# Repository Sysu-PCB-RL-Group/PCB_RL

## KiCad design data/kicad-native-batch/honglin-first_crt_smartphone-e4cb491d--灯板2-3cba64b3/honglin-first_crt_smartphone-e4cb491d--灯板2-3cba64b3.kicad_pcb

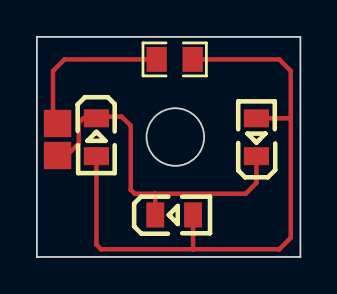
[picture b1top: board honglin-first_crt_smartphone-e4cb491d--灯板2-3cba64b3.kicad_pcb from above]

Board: 2 copper layers, 14.6 x 12.2 mm, 4 parts (0 on the bottom side), 2 nets.

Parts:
LED1, LED2, LED3: LED0805-R-RD
R2: R0805

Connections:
$1N488: LED1.1, LED2.1, LED3.1, R2.1
GND: LED1.2, LED2.2, LED3.2

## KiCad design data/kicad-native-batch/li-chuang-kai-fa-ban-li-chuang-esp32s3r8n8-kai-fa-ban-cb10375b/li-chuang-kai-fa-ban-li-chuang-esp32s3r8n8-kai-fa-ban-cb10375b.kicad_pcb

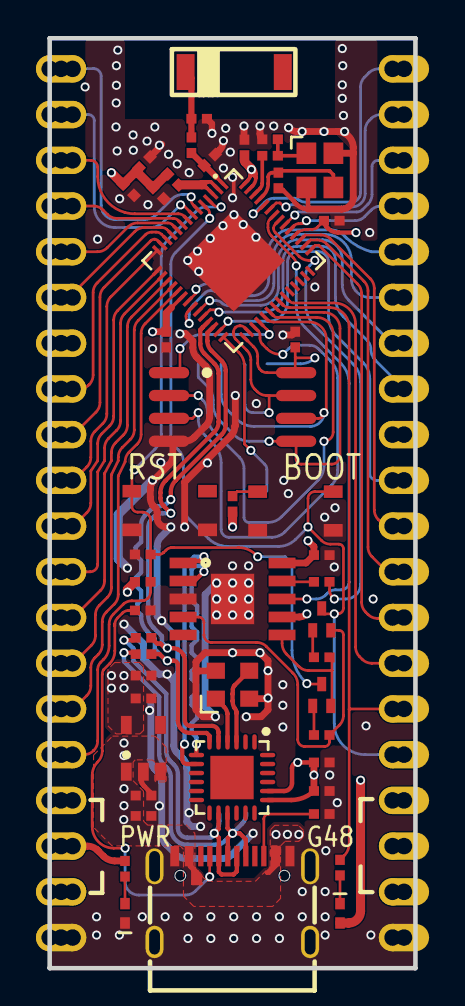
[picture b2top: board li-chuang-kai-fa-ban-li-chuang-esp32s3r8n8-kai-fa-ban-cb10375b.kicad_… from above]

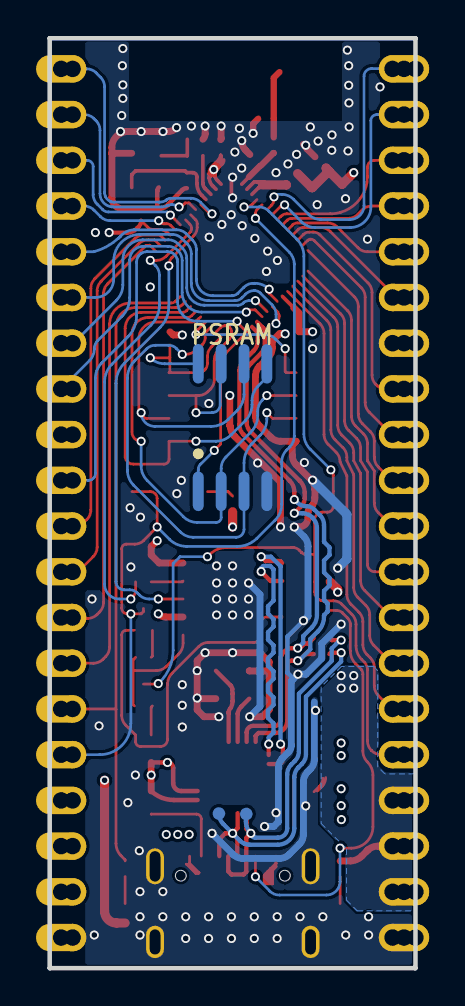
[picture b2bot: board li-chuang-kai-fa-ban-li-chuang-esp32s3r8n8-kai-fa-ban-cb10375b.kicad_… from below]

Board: 4 copper layers, 20.3 x 51.7 mm, 53 parts (3 on the bottom side), 67 nets.

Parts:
BOOT: KEY-SMD_4P-L4.2-W3.4-P2.15-LS4.5-TL
C19, C20, C21, C22, C23, C25, C33, C34, C41, C46, C47, C48, C49, C50, C51, C52, C53: R0402
C54: r0402
J1: 半孔-孔-20P-2.54-1.27-无丝印
J2: 半孔-孔-20p-2.54-1.27-无丝印
L4: R0402
L6, L7, L8: r0402
LED1: LED0402-RD_GREEN
PWR: LED0402-RD
Q1, Q2: SOT-523_L1.6-W0.8-P1.00-BL
R13, R14, R15, R16, R17, R18, R19, R22, R23, R24, R25: R0402
RST: KEY-SMD_4P-L4.2-W3.4-P2.15-LS4.5-TL
TP1, TP2: test-point-0.5mm
U2: TYPE-C-SMD_HX-TYPE-C-16PIN
U3: QFN-56_L7.0-W7.0-P0.40-TL-EP4.0
U4: SOP-8_L5.3-W5.3-P1.27-LS8.0-BL
U5: SOIC-8_L5.3-W5.3-P1.27-LS8.0-BL
U6: sot-23-5_l3.0-w1.7-p0.95-ls2.8-br
U16: qfn24_4x4
U24: ESOP-10_L4.9-W3.9-P1.00-LS6.2-BL-EP
U25: FILTER-SMD_L5.2-W2.0-L
X1: crystal-smd_4p-l2.5-w2.0-bl
X2: crystal-smd_4p-l2.5-w2.0-bl-a

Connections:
3V3: C19.2, C20.2, C21.2, C22.2, C41.2, C47.2, C48.2, C49.2, C50.2, C51.2, C53.2, J2.2, J2.3, J2.4, L4.1, LED1.2, R13.1, R14.2, R15.2, U3.20, U3.46, U3.55, U3.56, U6.5, U16.19, U16.20, U24.7, U24.10
340_RX: R24.2, U24.9
340_TX: U3.50, U24.8
$1N4043: R19.2, U2.B5
$1N4044: R18.2, U2.A5
$1N4117: BOOT.1, R14.1
$1N4141: PWR.2, R13.2
$1N4145: Q2.1, R16.2
$1N4146: Q1.1, R17.2
$1N12244: LED1.1, R25.1
$1N15135: L4.2, U3.2, U3.3
$1N27024: C54.2, L6.1, U3.1
$1N27033: C54.1, L7.1, U25.1
$1N27209: L8.1, U3.54
+5V: C46.2, C52.2, J1.2, J1.3, J1.4, U2.A4, U2.A9, U6.1, U6.3
CHIP_PU: C25.2, J2.5, Q2.3, R15.1, RST.4, U3.4
D3+: U16.8, U24.1
D3-: U16.7, U24.2
D4+: R22.2, U3.26, U16.6
D4-: R23.2, U3.25, U16.5
DTR: Q1.2, R16.1, U24.4
GND: BOOT.3, BOOT.4, C19.1, C20.1, C21.1, C22.1, C23.1, C25.1, C33.1, C34.2, C41.1, C46.1, C47.1, C48.1, C49.1, C50.1, C51.1, C52.1, C53.1, J1.1, J1.12, J2.1, J2.14, L6.2, L7.2, PWR.1, R18.1, R19.1, RST.1, RST.2, U2.1, U2.A1, U2.A12, U3.57, U4.4, U5.4, U6.2, U6.4, U16.0, U24.3, U24.11, X1.2, X1.4, X2.2, X2.4
GPIO0: BOOT.2, J1.5, Q1.3, U3.5
GPIO1: J2.20, U3.6
GPIO2: J2.19, U3.7
GPIO3: J2.18, U3.8
GPIO4: J2.17, U3.9
GPIO5: J2.16, U3.10
GPIO6: J2.15, U3.11
GPIO7: J2.13, U3.12
GPIO8: J2.12, U3.13
GPIO9: J2.11, U3.14
GPIO10: J2.10, U3.15
GPIO11: J2.9, U3.16
GPIO12: J2.8, U3.17
GPIO13: J2.7, U3.18
GPIO14: J2.6, U3.19
GPIO15: J1.16, U3.21
GPIO16: J1.15, U3.22
GPIO17: J1.14, U3.23
GPIO18: J1.13, U3.24
GPIO21: J1.11, U3.27
GPIO38: J1.8, U3.43
GPIO39: J1.9, U3.44
GPIO40: J1.10, U3.45
GPIO41: J1.17, U3.47
GPIO42: J1.18, U3.48
GPIO45: J1.19, U3.51
GPIO46: J1.20, U3.52
GPIO47: J1.7, U3.37
GPIO48: J1.6, R25.2, U3.36
RTS: Q2.2, R17.1, U24.6
SPICLK: U3.33, U4.6, U5.6
SPICS0: U3.32, U5.1
SPICS1: U3.28, U4.1
SPID: U3.35, U4.5, U5.5
SPIHD: U3.30, U4.7, U5.7
SPIQ: U3.34, U4.2, U5.2
SPIWP: U3.31, U4.3, U5.3
U0TX: R24.1, U3.49
USB_D+: R22.1, TP1.1, U2.A6, U2.B6, U16.15
USB_D-: R23.1, TP2.1, U2.A7, U2.B7, U16.14
VDD_SPI: C23.2, U3.29, U4.8, U5.8
XIN: U16.4, X2.1
XOUT: U16.3, X2.3
XTAL_N: C34.1, U3.53, X1.3
XTAL_P: C33.2, L8.2, X1.1

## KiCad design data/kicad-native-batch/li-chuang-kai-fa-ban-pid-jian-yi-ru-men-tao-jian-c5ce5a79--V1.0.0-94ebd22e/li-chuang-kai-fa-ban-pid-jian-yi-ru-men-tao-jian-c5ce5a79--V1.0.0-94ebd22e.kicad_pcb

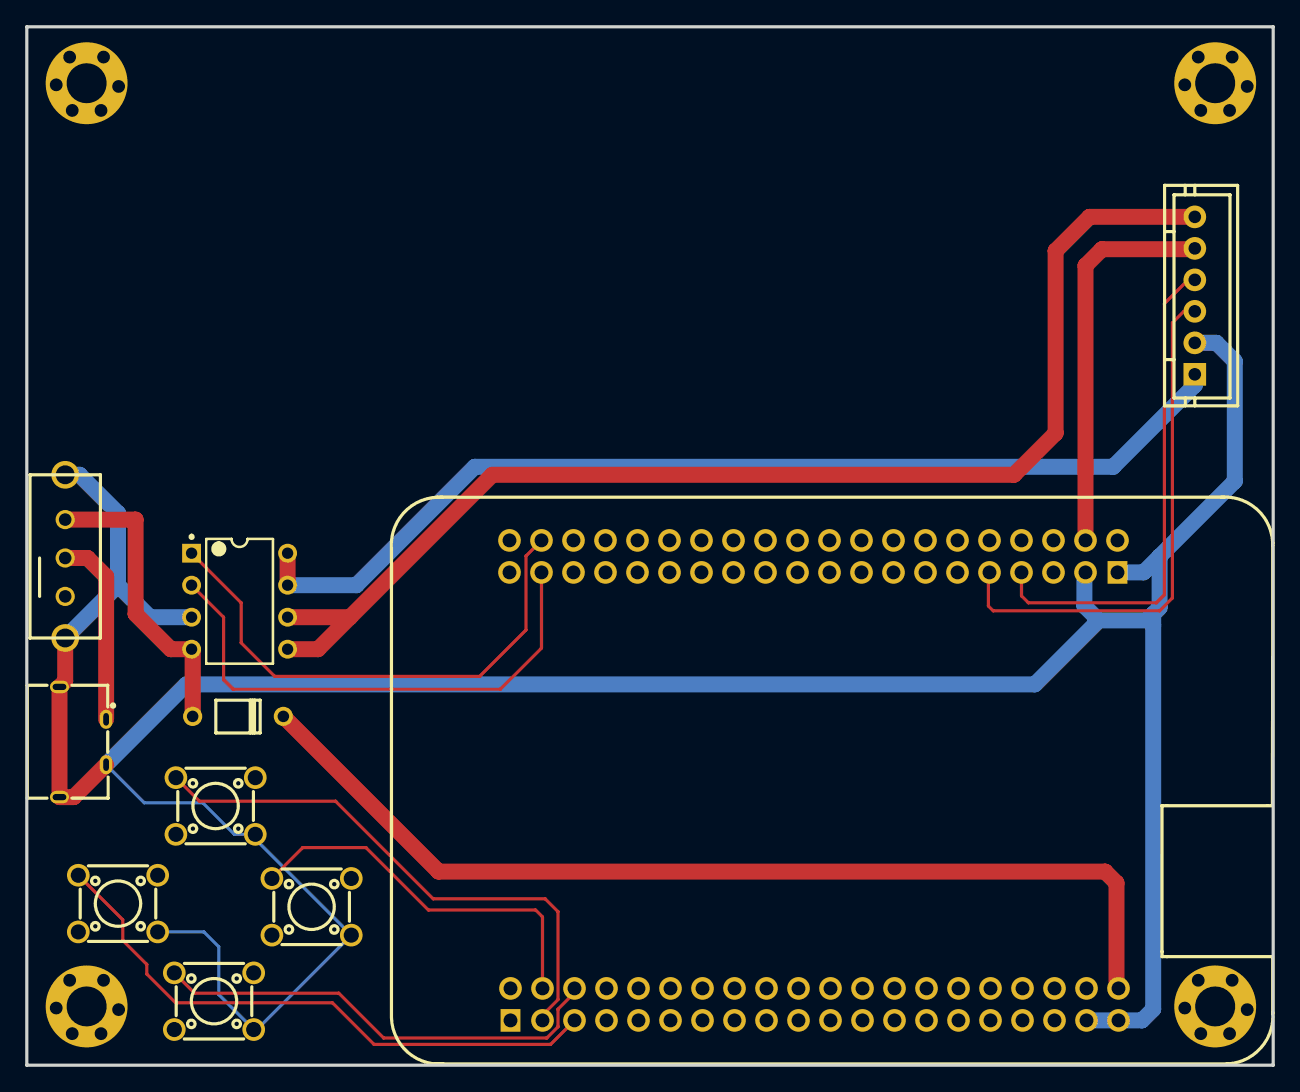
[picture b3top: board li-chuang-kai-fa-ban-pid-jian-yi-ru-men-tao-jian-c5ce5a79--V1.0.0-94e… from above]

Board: 2 copper layers, 98.9 x 82.4 mm, 15 parts (0 on the bottom side), 15 nets.

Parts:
H1, H2, H3, H4: m3 125x300
U4, U5, U6, U7: SW-TH_4P-L6.0-W6.0-P4.50-LS6.3
U8: DIP-8_L9.3-W6.4-P2.54-LS7.6-BL-1
U9: CONN-TH_6P-P2.50_HCTL_XH-6A_C2908604
U10: COMM-TH_LCKFB-TMX-MSPM0G3507
U11: TT马达
U12: DIO-TH_BD2.4-L3.2-P7.20-D0.8-RD
开关1: SW-TH_SK-12E12-G5
电源1: USB-SMD_KH-TYPE-C-2P

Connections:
3V3: U9.5, U10.44
$1N706: 开关1.2, 电源1.1
$1N1740: U8.5, U8.6, U9.6
$1N1765: U8.7, U8.8, U9.1
+5V: U10.40, U12.1
BI: U8.1, U10.78
ENCODER-A: U9.3, U10.49
ENCODER-B: U9.4, U10.47
FI: U8.2, U10.77
GND: U4.4, U5.4, U6.4, U7.4, U8.3, U9.2, U10.37, U10.39, U10.41, U10.43, 开关1.4, 开关1.5, 电源1.2, 电源1.3, 电源1.4
KEY_DOWN: U7.1, U10.6
KEY_LEFT: U5.1, U10.5
KEY_RIGHT: U6.1, U10.4
KEY_UP: U4.1, U10.3
MOTOR-VCC: U8.4, U12.2, 开关1.3

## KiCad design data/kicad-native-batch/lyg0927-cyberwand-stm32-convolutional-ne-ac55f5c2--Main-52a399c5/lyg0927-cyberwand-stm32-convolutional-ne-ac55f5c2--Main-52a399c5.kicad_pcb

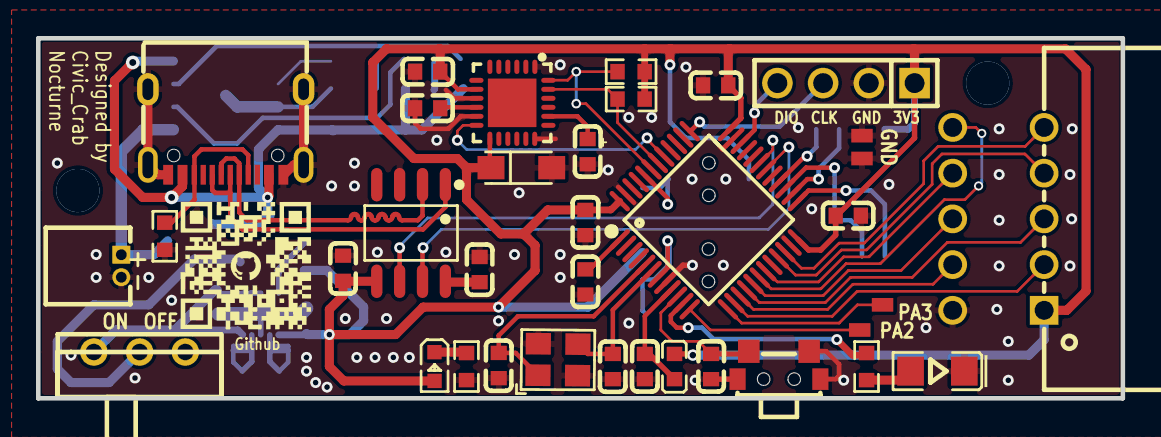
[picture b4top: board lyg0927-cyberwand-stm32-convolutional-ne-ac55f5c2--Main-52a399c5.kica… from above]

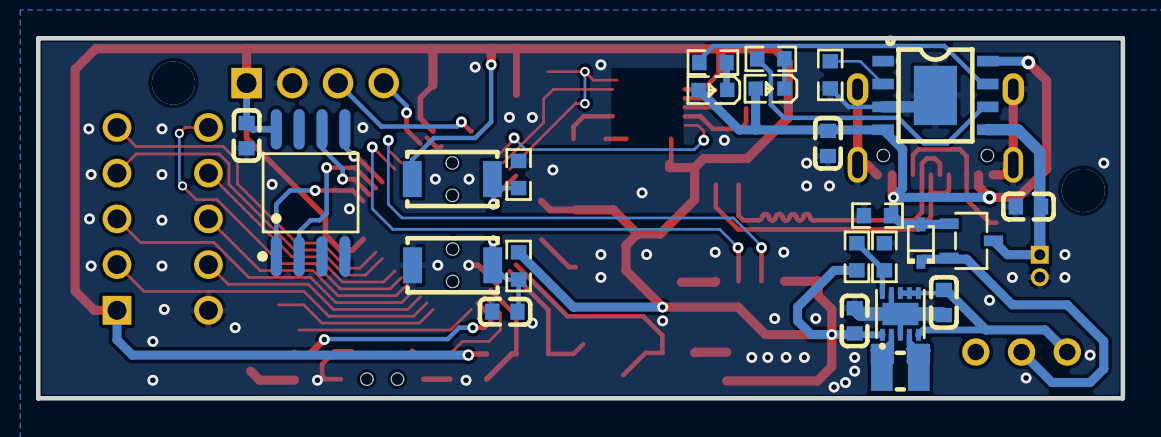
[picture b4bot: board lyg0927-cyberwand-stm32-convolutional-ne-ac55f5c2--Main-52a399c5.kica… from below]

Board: 2 copper layers, 60.3 x 20.0 mm, 56 parts (24 on the bottom side), 49 nets.

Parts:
BAT1: CONN-TH_2P-P1.25_HCTL_HC-1.25-2AW
BOOT0: KEY-SMD_L3.9-W3.0-LS5.0-EH
C1, C2, C3, C4, C7, C8, C9, C10, C11, C12, C13, C14, C15, C17, C18, C19, C20, C21, C22: C0603
C16: CAP-SMD_L3.2-W1.6-RD
Control: SW-SMD_TS24CA
D2: SOD-323_L1.7-W1.3-LS2.5-FD
L1: IND-SMD_L2.5-W2.0
L2: L0603
LED1: LED0603-RD
LED2, LED3: LED0603-RD_RED
PROG0: R0603
Q1: SOT-23-3_L2.9-W1.6-P1.90-LS2.8-BR
R1, R2, R3, R4, R5, R6, R7, R8, R9, R10, R11, R12: R0603
RST0: KEY-SMD_L3.9-W3.0-LS5.0-EH
RT6150: WSON-10_L2.5-W2.5-P0.50-BL-EP
STLink: HDR-TH_4P-P2.54-V-M
SW1: SW-TH_3P-L9.1-W3.5-P2.50-A3
Signal: LED1206-R-RD_RED
Slot: CONN-TH_10P-P2.54_WINGTAT_ER10BGFBK
TP4056: ESOP-8_L4.9-W3.9-P1.27-LS6.0-BL-EP
U1: LQFP-48_L7.0-W7.0-P0.50-LS9.0-BL
U2: SOP-8_L4.9-W3.9-P1.27-LS6.0-BL
U3: SOIC-8_L5.3-W5.3-P1.27-LS8.0-BL
U4: QFN-24_L4.0-W4.0-P0.50-BL-EP2.7
USB1: USB-C-SMD_TYPE-C-6PIN-2MD-073
X1: OSC-SMD_4P-L3.2-W2.5-BL

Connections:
3V3: BOOT0.2, C4.1, C8.1, C9.1, C10.1, C11.1, C16.1, C20.1, C22.1, L2.2, LED3.2, R5.2, R7.1, R8.1, R11.1, RT6150.1, STLink.1, Slot.1, U1.24, U1.36, U1.48, U2.5, U3.8, U4.8, U4.13
$1N1926: L1.2, RT6150.2
$1N2095: R5.1, R6.2, RT6150.10
$1N5022: C7.1, U2.8
$1N9764: R1.2, USB1.4, USB1.10
$1N10379: LED2.1, R3.2
$1N10382: LED1.1, R2.2
$1N10530: R3.1, TP4056.7
$1N10534: R2.1, TP4056.6
$1N10716: PROG0.2, TP4056.2
$1N11756: BAT1.1, C2.1, Q1.3, TP4056.5
$1N13991: C12.1, L2.1, U1.9
$1N14717: R9.2, Signal.1
$1N14914: LED3.1, R10.1
$1N21597: L1.1, RT6150.4
$1N22177: D2.2, Q1.2, SW1.2
$1N22183: C3.1, RT6150.5, RT6150.6, RT6150.7, RT6150.8, SW1.1
$1N34559: C15.2, U4.10
$1N43151: C21.1, U4.20
BOOT0: BOOT0.1, R12.2, U1.44
D+: U2.1, USB1.6, USB1.8
D-: U2.2, USB1.5, USB1.7
GND: BAT1.2, C1.2, C2.2, C3.2, C4.2, C7.2, C8.2, C9.2, C10.2, C11.2, C12.2, C13.1, C14.1, C15.1, C16.2, C17.2, C18.2, C19.2, C20.2, C21.2, C22.2, Control.1, Control.2, Control.3, PROG0.1, R1.1, R4.2, R6.1, R10.2, R12.1, RST0.2, RT6150.3, RT6150.9, RT6150.11, STLink.2, Signal.2, Slot.2, TP4056.1, TP4056.3, TP4056.9, U1.8, U1.23, U1.35, U1.47, U2.3, U3.4, U4.1, U4.9, U4.11, U4.18, USB1.1, USB1.12, USB1.13, USB1.14, X1.2, X1.4
NRST: C17.1, R11.2, RST0.1, U1.7
OSC_IN: C13.2, U1.5, X1.1
OSC_OUT: C14.2, U1.6, X1.3
PA0: C19.1, Control.4, U1.10
PA1_LED: R9.1, U1.11
PA4_CSS: Slot.3, U1.14
PA5_SCK: Slot.4, U1.15
PA6_MISO: Slot.5, U1.16
PA7_MOSI: Slot.6, U1.17
PA13_DIO: STLink.4, U1.34
PA14_CLK: STLink.3, U1.37
PB0_CUS: Slot.10, U1.18
PB1_ADC: Slot.8, U1.19
PB5_INT1: U1.41, U4.12
PB6_SCL: R8.2, U1.42, U4.23
PB7_SDA: R7.2, U1.43, U4.24
PB10_SCL_TX: Slot.7, U1.21
PB11_SDA_RX: Slot.9, U1.22
RXD: U1.30, U2.7
SPI2_CS: U1.25, U3.1
SPI2_MISO: U1.27, U3.2
SPI2_MOSI: U1.28, U3.5
SPI2_SCK: U1.26, U3.6
TXD: U1.31, U2.6
VBAT_E: C18.1, U1.1
VCC_USB: C1.1, D2.1, LED1.2, LED2.2, Q1.1, R4.1, TP4056.4, TP4056.8, USB1.2, USB1.11

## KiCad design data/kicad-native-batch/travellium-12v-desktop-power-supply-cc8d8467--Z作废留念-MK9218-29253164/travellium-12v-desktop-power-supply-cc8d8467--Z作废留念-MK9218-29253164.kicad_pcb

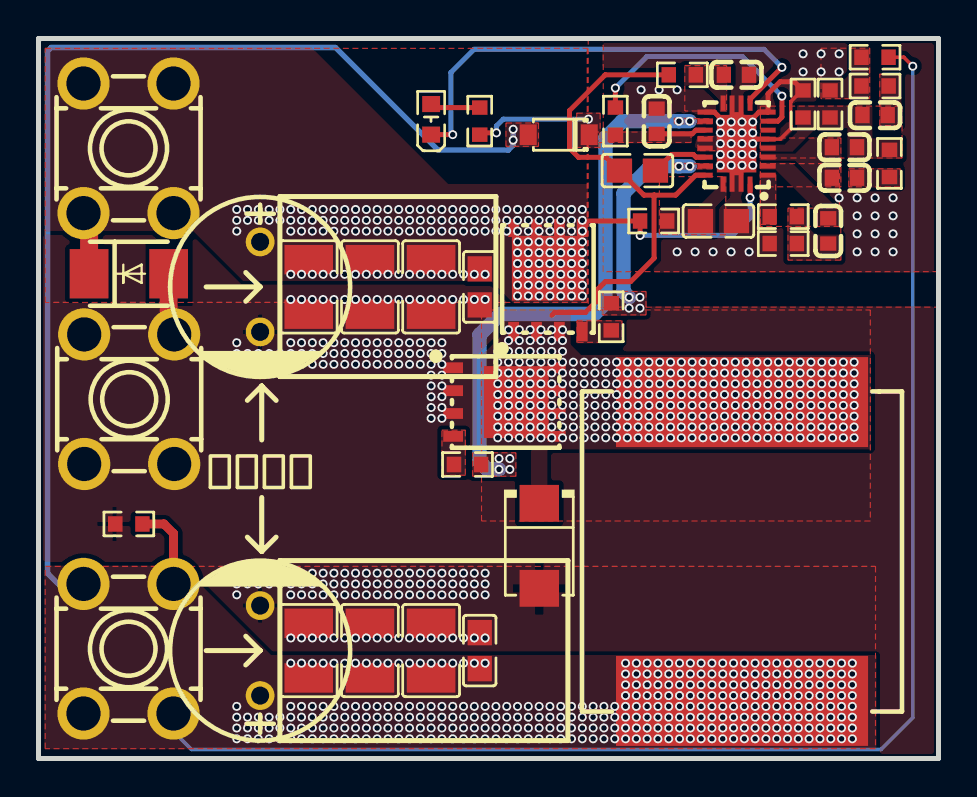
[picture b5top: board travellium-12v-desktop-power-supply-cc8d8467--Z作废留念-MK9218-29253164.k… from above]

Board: 2 copper layers, 50.0 x 40.0 mm, 43 parts (0 on the bottom side), 23 nets.

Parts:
C1: CAP-TH_BD10.0-P5.00-D0.6-FD_2
C2, C3, C4, C6, C7, C8: C1210
C5, C9, C11, C17: C0805
C10, C12, C13, C14, C15, C16: C0603
D1: SMB_L4.4-W3.6-LS5.3-L-FD
D2: SMB_L4.6-W3.6-LS5.3-RD
D3: SOD-123_L2.8-W1.8-LS3.7-RD
L1: IND-SMD_L17.5-W17.5
LED1: LED0603-RD_1
Q1, Q2: PG-TDSON-8_L5.9-W5.1-P1.27-LS6.1-BL
R1, R2, R3, R4, R5, R6, R7, R8, R9, R10, R11, R12, R13, R14: R0603
U1: CAP-TH_BD10.0-P5.00-D0.6-FD
U2: VQFN-20_L4.5-W3.5-P0.50-BL-EP_TI_RHL0020A
U3, U4, U5: CONN-TH_T44001

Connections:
$1N5923: C13.1, R7.1
$1N5928: C13.2, C14.1, R6.1, R11.1, R14.2, U2.5
$1N6075: R5.1, R6.2, R7.2
$1N31770: C12.2, R8.1, R13.2
$1N31791: C12.1, U2.3
$1N31948: C17.1, R2.1, U2.20
$1N32058: C16.2, D3.1, R9.2, R10.2, U2.14
$1N32091: R10.1, U2.8
$1N32186: LED1.2, R9.1
$1N32326: R4.2, U2.13
$1N32622: C11.2, U2.17
$1N32707: R3.2, U2.18
$1N32717: C15.2, R12.2, U2.11
$1N34967: LED1.1, U2.10
$1N37231: R8.2, U2.2
$1N38925: C10.1, R11.2
$1N38932: C10.2, C14.2, U2.4
GH: Q1.4, R3.1
GL: Q2.4, R4.1
GND: C1.2, C2.1, C3.1, C4.1, C5.1, C6.1, C7.1, C8.1, C9.1, C15.1, C16.1, C17.2, D1.1, D2.2, Q2.1, Q2.2, Q2.3, R1.1, R13.1, R14.1, U1.2, U2.6, U2.9, U2.12, U2.15, U2.16, U2.21, U5.1, U5.2, U5.3, U5.4
P12V: C6.2, C7.2, C8.2, C9.2, D3.2, L1.2, R1.2, R5.2, U1.1, U4.1, U4.2, U4.3, U4.4
P60V: C1.1, C2.2, C3.2, C4.2, C5.2, D1.2, Q1.5, Q1.6, Q1.7, Q1.8, R2.2, U2.1, U3.1, U3.2, U3.3, U3.4
SW: C11.1, D2.1, L1.1, Q1.1, Q1.2, Q1.3, Q2.5, Q2.6, Q2.7, Q2.8, R12.1, U2.19

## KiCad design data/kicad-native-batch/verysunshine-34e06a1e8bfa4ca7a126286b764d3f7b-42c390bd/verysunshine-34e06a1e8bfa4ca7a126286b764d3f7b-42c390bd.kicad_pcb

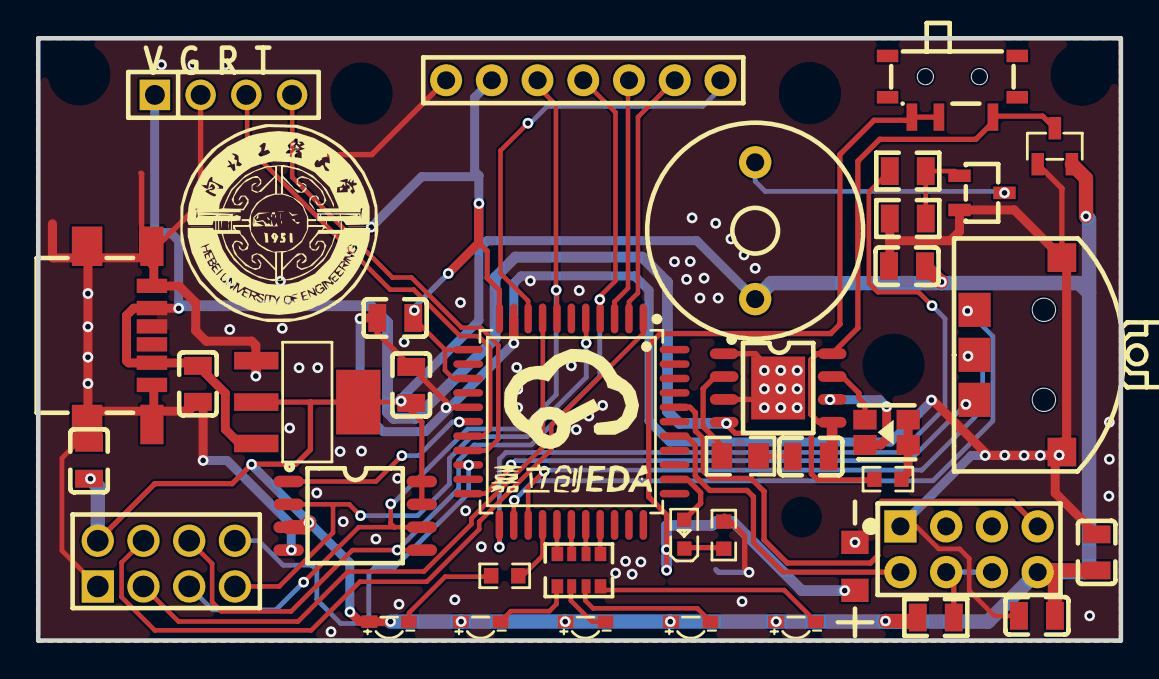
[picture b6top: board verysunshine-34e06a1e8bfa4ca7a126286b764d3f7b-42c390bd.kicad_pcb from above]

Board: 2 copper layers, 60.1 x 33.5 mm, 39 parts (1 on the bottom side), 42 nets.

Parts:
1: 0805
BUZZER1: BUZ-TH_BD12.0-P7.60-D0.6-FD
C1, C2, C9, C13, C16, C17, C21, C22: C0805
H3: HDR-TH_4P-P2.54-V-M
LED1, LED2, LED3, LED4, LED13: LED-SMD_L2.1-W1.0-R-RD
LED5: LED-ARRAY-SMD_4P-L3.2-W2.7_E6C1209SEQBC2UDA
LED14: LED0603-RD_BLUE
MK1: WIRELM-NRF24L01
Q4: SOT-23-3_L3.0-W1.7-P0.95-LS2.9-BR
R1: R0805(2)
R13, R14: R0805(1)
R22, R23, R24: R0603
RN1: RES-ARRAY-SMD_0603-8P-L3.2-W1.6-BL
SW11: SW-SMD_TM-2022-3
SW13: SW-TH_MSK12C02
U1: LQFP-44_L10.0-W10.0-P0.80-LS12.0-BL
U3, U10: 电池座
U4: SOIC-8_L5.3-W5.3-P1.27-LS8.0-BL
U5: WT-01S
U7: SOP-8_L4.9-W3.9-P1.27-LS6.0-BL-EP
U8: OLED-12864(7PIN-SPI)
U9: SOT-223-4_L6.5-W3.5-P2.30-LS7.0-BR
U11: SOT-23-3_L2.9-W1.3-P1.90-LS2.4-BR
USB1: USB-C-SMD_TYC-249D

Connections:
$1N559: BUZZER1.2, Q4.3
$1N584: Q4.1, R13.1, R14.1
$1N669: LED13.2, R24.1
$1N709: LED14.1, R23.1
$1N821: R1.2, U5.6, U5.7
$1N17643: LED1.2, RN1.5
$1N17699: LED2.2, RN1.6
$1N17755: LED3.2, RN1.7
$1N17811: LED4.2, RN1.8
$1N51830: 1.2, U7.2
$1N51836: LED5.1, LED5.3, R22.1
$1N51837: LED5.4, U7.7
$1N51838: LED5.2, U7.6
$1N53808: C9.2, SW13.1, U7.5, U7.8, U11.3
$1N54478: SW13.2, SW13.3, U3.1, U10.1
+3.3V: BUZZER1.1, C2.2, C13.1, C16.1, C17.1, C21.2, C22.2, LED1.1, LED2.1, LED3.1, LED4.1, LED13.1, MK1.2, R1.1, U1.11, U1.12, U1.14, U4.3, U4.7, U4.8, U5.8, U8.2, U9.2, U9.4, U11.2
BEEP: R13.2, U1.23
CH_RX: H3.4, U1.19
CH_TX: H3.3, U1.18
ESP_RXD: U1.40, U5.4
ESP_TXD: U1.38, U5.5
FUNCTION_1: R24.2, U1.26
FUNCTION_2: RN1.4, U1.27
FUNCTION_3: RN1.3, U1.28
FUNCTION_4: RN1.2, U1.29
FUNCTION_5: RN1.1, U1.30
GND: 1.1, C1.1, C2.1, C9.1, C13.2, C16.2, C17.2, C21.1, C22.1, H3.2, MK1.1, Q4.2, R14.2, R23.2, SW11.a, U1.10, U1.16, U3.2, U4.4, U5.1, U7.1, U7.3, U7.9, U8.1, U9.1, U10.2, U11.1, USB1.7, USB1.8, USB1.9, USB1.10, USB1.A12, USB1.B12
KEY_1: SW11.b, U1.22
KEY_2: SW11.c, U1.25
KEY_3: SW11.d, U1.24
LED: LED14.2, U1.35
NRF_CS: MK1.3, U1.8
NRF_CSN: MK1.4, U1.1
NRF_IRQ: MK1.8, U1.20
OLED_CS: U1.9, U8.7
OLED_D/C: U1.2, U8.6
OLED_RES: U1.3, U8.5
RAM_CS: U1.17, U4.1
SPI_MISO: MK1.7, U1.5, U4.2
SPI_MOSI: MK1.6, U1.4, U4.5, U8.4
SPI_SCK: MK1.5, U1.7, U4.6, U8.3
USB_VBUS: C1.2, H3.1, R22.2, U7.4, U9.3, USB1.A9, USB1.B9
